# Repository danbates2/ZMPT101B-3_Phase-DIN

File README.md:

# ZMPT101B-3_Phase DIN
 
https://uk.rs-online.com/web/p/din-rail-enclosures/1947584/

https://docs.rs-online.com/9e24/A700000006545745.pdf

This is not a fully tested and certified device and as such cannot be regarded as safe.

NOT SAFE for use.

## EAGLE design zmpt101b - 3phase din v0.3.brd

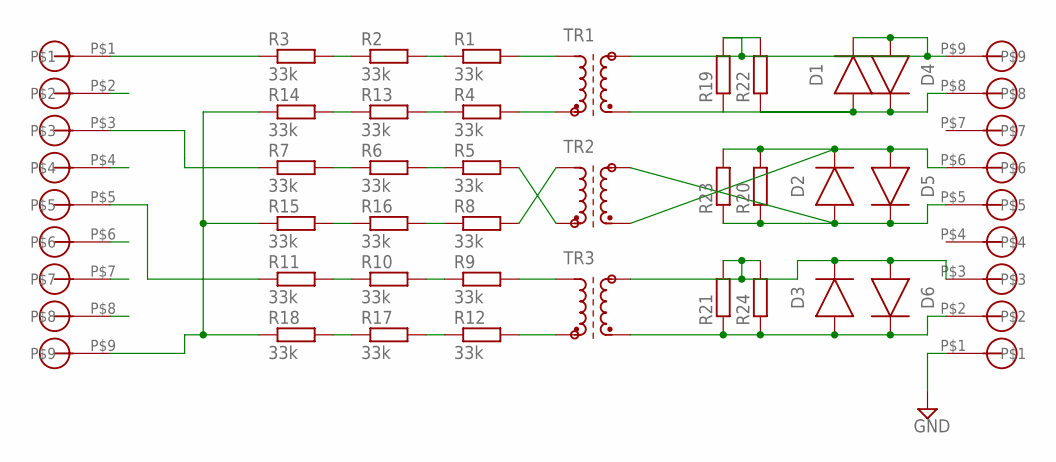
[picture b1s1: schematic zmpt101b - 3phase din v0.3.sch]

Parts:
D1, D2, D3, D4, D5, D6: DIODE_DO-219-AB(SOD123F); SODFL3718X115
R1, R2, R3, R4, R5, R6, R7, R8, R9, R10, R11, R12, R13, R14, R15, R16, R17, R18: 33k; R1206
R19, R20, R21: 110R; R0603
R22, R23, R24: R-EU_0207/12; 0207/12
TR1, TR2, TR3: ZMPT101B
U$1, U$2: 5MMBLOCK_X9; 9/5.08

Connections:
GND: U$2.P$1
unnamed: R3.1, U$1.P$1
unnamed: R2.1, R3.2
unnamed: R1.1, R2.2
unnamed: R1.2, TR1.P$4 (A1)
unnamed: R4.2, TR1.P$3 (E1)
unnamed: R14.1, R15.1, R18.1, U$1.P$9
unnamed: R7.1, U$1.P$3
unnamed: R6.1, R7.2
unnamed: R5.1, R6.2
unnamed: R8.2, TR2.P$4 (A1)
unnamed: R5.2, TR2.P$3 (E1)
unnamed: R11.1, U$1.P$5
unnamed: R10.1, R11.2
unnamed: R9.1, R10.2
unnamed: R9.2, TR3.P$4 (A1)
unnamed: R12.2, TR3.P$3 (E1)
unnamed: D2.2 (A), D5.1 (C), R20.1, R23.1, TR2.P$1 (A2), U$2.P$5
unnamed: D2.1 (C), D5.2 (A), R20.2, R23.2, TR2.P$2 (E2), U$2.P$6
unnamed: D1.2 (A), D4.1 (C), R19.1, R22.1, TR1.P$2 (E2), U$2.P$8
unnamed: D1.1 (C), D4.2 (A), R19.2, R22.2, TR1.P$1 (A2), U$2.P$9
unnamed: D3.2 (A), D6.1 (C), R21.1, R24.1, TR3.P$2 (E2), U$2.P$2
unnamed: R4.1, R13.2
unnamed: R13.1, R14.2
unnamed: R8.1, R16.2
unnamed: R15.2, R16.1
unnamed: R12.1, R17.2
unnamed: R17.1, R18.2
unnamed: D3.1 (C), D6.2 (A), R21.2, R24.2, TR3.P$1 (A2), U$2.P$3
P$4: U$2.P$4
P$7: U$2.P$7

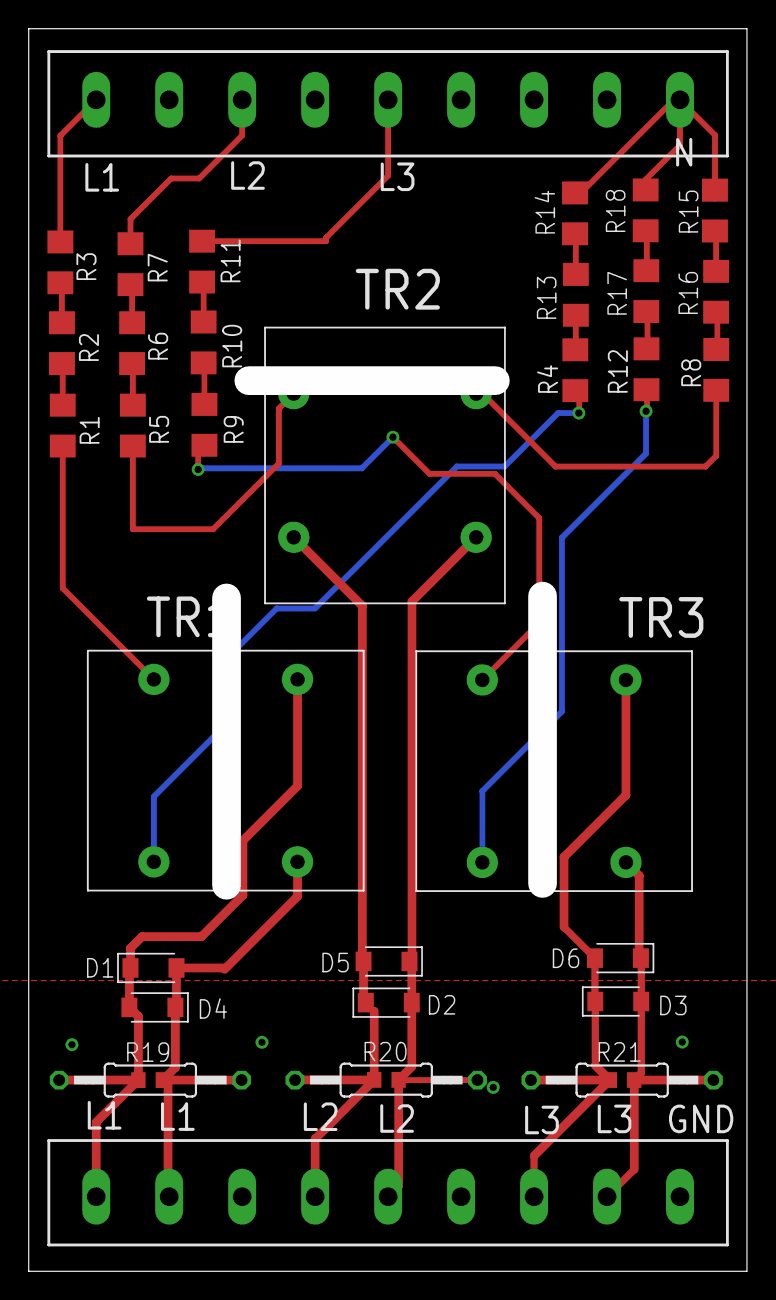
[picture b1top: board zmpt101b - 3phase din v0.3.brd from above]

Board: 2 copper layers, 48.0 x 84.5 mm, 35 parts (0 on the bottom side), 28 nets.

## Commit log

2020-08-19 init
2020-08-19 1st version
2020-08-21 commit v0.1 for prototyping
2020-11-04 v0.2 out for PCB prototype.
2021-01-22 sync
